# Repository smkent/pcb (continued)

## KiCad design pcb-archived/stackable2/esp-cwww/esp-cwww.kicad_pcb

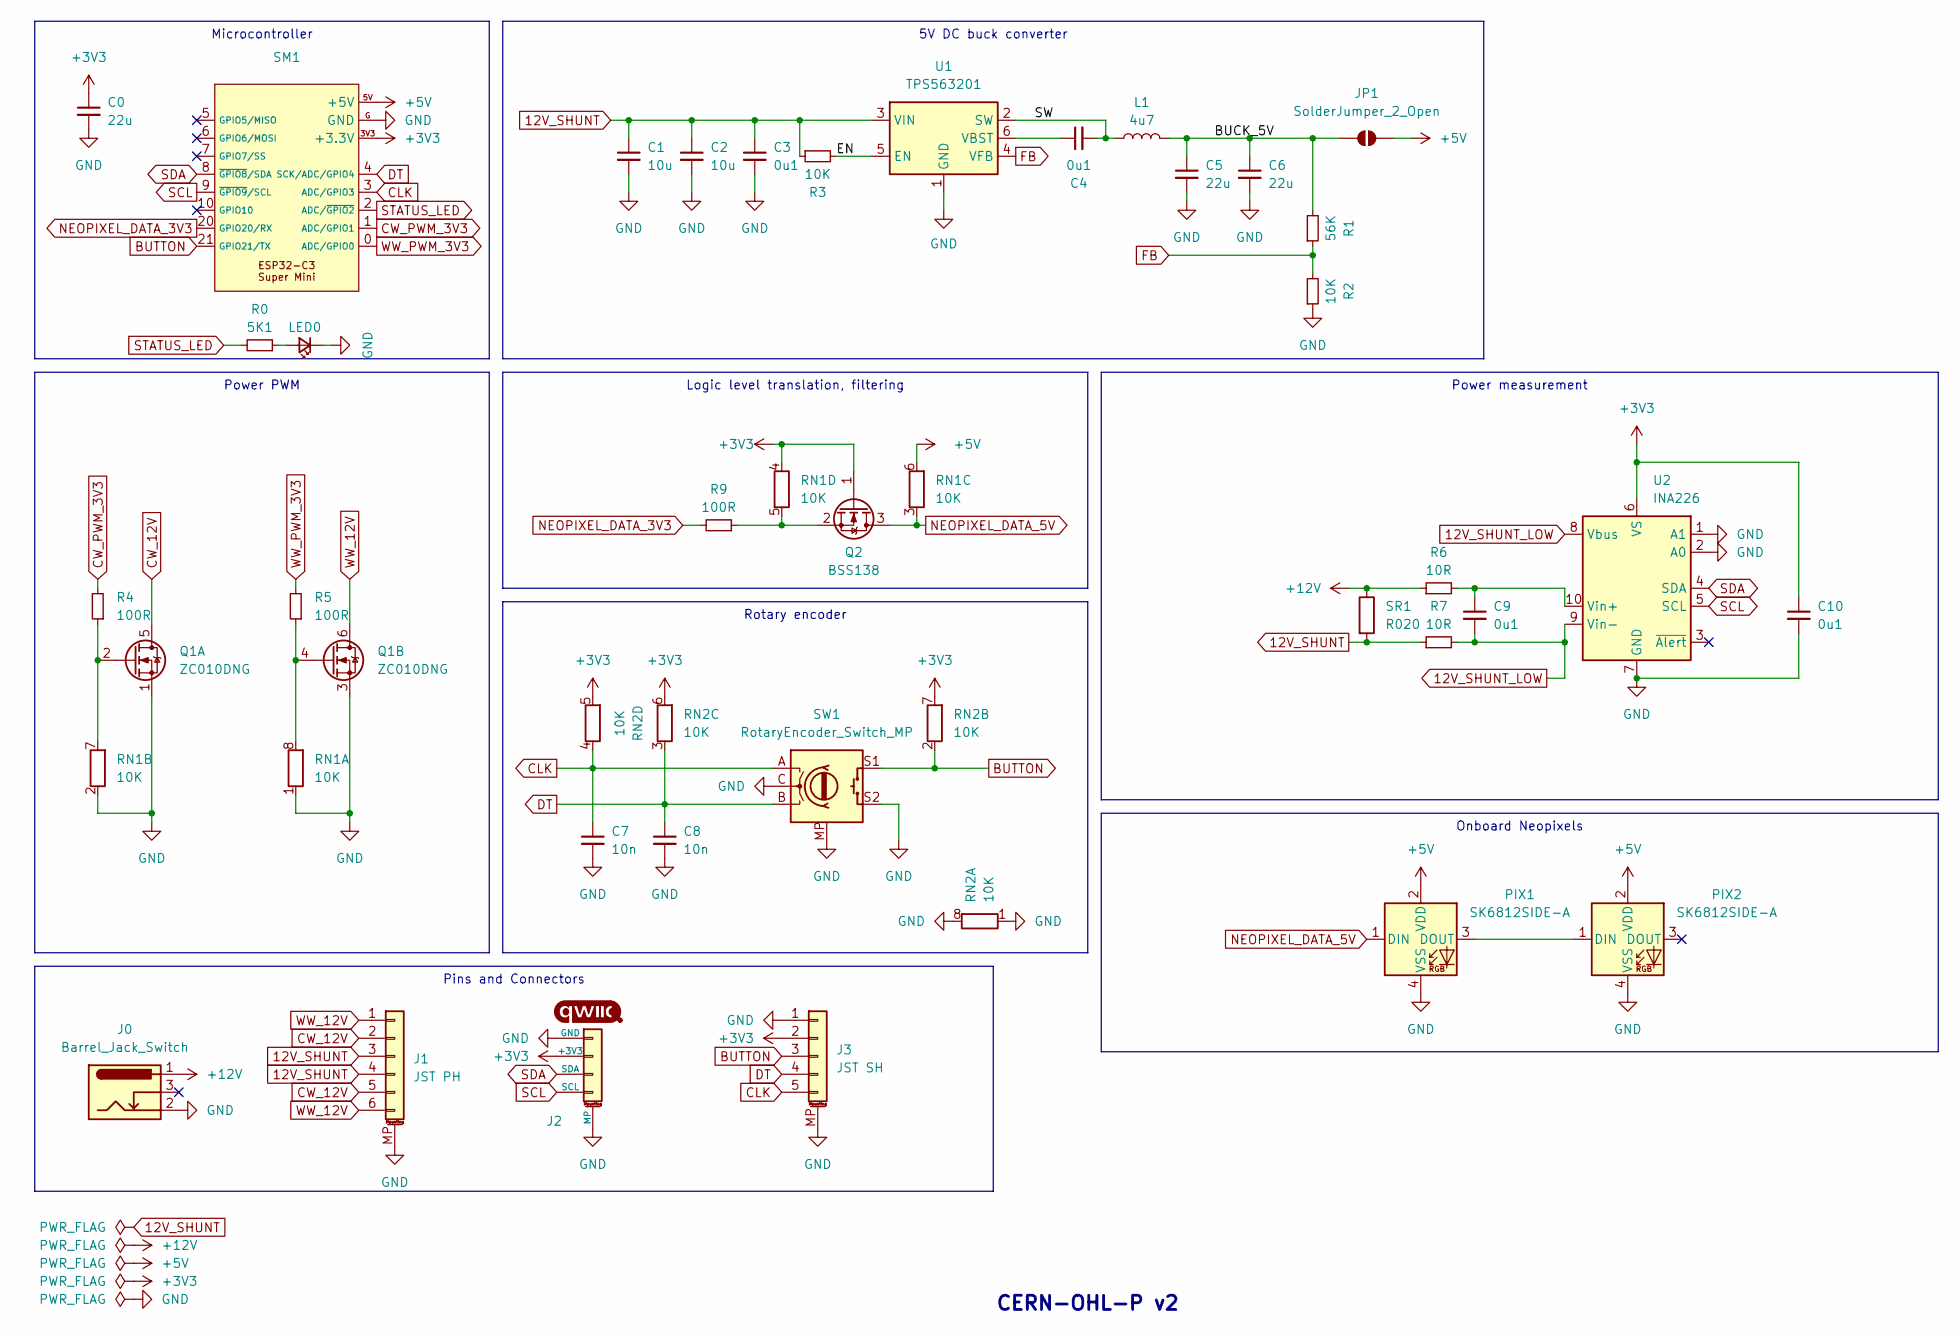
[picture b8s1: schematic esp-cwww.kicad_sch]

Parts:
C0, C5, C6: 22u; C_0603_1608Metric_Pad1.08x0.95mm_HandSolder
C1, C2: 10u; C_0603_1608Metric_Pad1.08x0.95mm_HandSolder
C3, C4: 0u1; C_0603_1608Metric_Pad1.08x0.95mm_HandSolder
C7, C8: 10n; C_0603_1608Metric_Pad1.08x0.95mm_HandSolder
C9, C10: 0u1; C_0402_1005Metric; LCSC Part C152814
J0: Barrel_Jack_Switch; BarrelJack_DC-050_SMT_Horizontal
J1: JST PH; JST_PH_S6B-PH-SM4-TB_1x06-1MP_P2.00mm_Horizontal
J2: Qwiic; Qwiic-SMD-horizontal-logo
J3: JST SH; JST_SH_SM05B-SRSS-TB_1x05-1MP_P1.00mm_Horizontal
JP1: SolderJumper_2_Open; SolderJumper-2_P1.3mm_Open_TrianglePad1.0x1.5mm
L1: 4u7; L_1008_2520Metric
LED0: LED_Small; LED_0603_1608Metric_Pad1.05x0.95mm_HandSolder_simple
PIX1, PIX2: SK6812SIDE-A; LED_SK6812SIDE-A_4.0x1.6mm; LCSC Part C2890037
Q1: ZC010DNG; PDFN-8_L3.2-W3.1-P0.65-LS3.4-BL-EP2; LCSC Part C36499170
Q2: BSS138; SOT-23
R0: 5K1; R_0402_1005Metric
R1: 56K; R_0603_1608Metric_Pad0.98x0.95mm_HandSolder
R2, R3: 10K; R_0603_1608Metric_Pad0.98x0.95mm_HandSolder
R4, R5, R9: 100R; R_0603_1608Metric_Pad0.98x0.95mm_HandSolder
R6, R7: 10R; R_0402_1005Metric; LCSC Part C25077
RN1, RN2: 10K; R_Array_Convex_4x0603
SM1: ESP32-C3-Super-Mini-Castellated-SMD-only
SR1: R020; R_2512_6332Metric_Pad1.40x3.35mm_HandSolder; LCSC Part C5375467
SW1: RotaryEncoder_Switch_MP; RotaryEncoder_Alps_EC11-Switch_Combo_H20mm
U1: TPS563201; SOT-23-6
U2: INA226; VSSOP-10_3x3mm_P0.5mm

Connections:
12V_SHUNT: C1.1, C2.1, C3.1, J1.3, J1.4, R3.1, R7.1, SR1.2, U1.3 (VIN)
12V_SHUNT_LOW: C9.2, R7.2, U2.8 (Vbus), U2.9 (Vin-)
+3V3: C0.1, C10.1, J2.2 (+3V3), J3.2, Q2.1 (G), RN1.4 (R4.1), RN2.5 (R4.2), RN2.6 (R3.2), RN2.7 (R2.2), SM1.3V3 (+3.3V), U2.6 (VS)
+5V: JP1.2 (B), PIX1.2 (VDD), PIX2.2 (VDD), RN1.6 (R3.2), SM1.5V (+5V)
+12V: J0.1, R6.1, SR1.1
/BUCK_5V: C5.1, C6.1, JP1.1 (A), L1.2, R1.2
/EN: R3.2, U1.5 (EN)
/SW: C4.2, L1.1, U1.2 (SW)
BUTTON: J3.3, RN2.2 (R2.1), SM1.21 (GPIO21/TX), SW1.S1
CLK: C7.1, J3.5, RN2.4 (R4.1), SM1.3 (ADC/GPIO3), SW1.A
CW_12V: J1.2, J1.5, Q1.5 (D)
CW_PWM_3V3: R4.2, SM1.1 (ADC/GPIO1)
DT: C8.1, J3.4, RN2.3 (R3.1), SM1.4 (SCK/ADC/GPIO4), SW1.B
FB: R1.1, R2.2, U1.4 (VFB)
GND: C0.2, C1.2, C2.2, C3.2, C5.2, C6.2, C7.2, C8.2, C10.2, J0.2, J1.MP (MountPin), J2.1 (GND), J2.MP, J3.1, J3.MP (MountPin), LED0.1 (K), PIX1.4 (VSS), PIX2.4 (VSS), Q1.1 (S), Q1.3 (S), R2.1, RN1.1 (R1.1), RN1.2 (R2.1), RN2.1 (R1.1), RN2.8 (R1.2), SM1.G (GND), SW1.C, SW1.MP, SW1.S2, U1.1 (GND), U2.1 (A1), U2.2 (A0), U2.7 (GND)
NEOPIXEL_DATA_3V3: R9.2, SM1.20 (GPIO20/RX)
NEOPIXEL_DATA_5V: PIX1.1 (DIN), Q2.3 (D), RN1.3 (R3.1)
unnamed: LED0.2 (A), R0.1
unnamed: PIX1.3 (DOUT), PIX2.1 (DIN)
unnamed: Q1.2 (G), R4.1, RN1.7 (R2.2)
unnamed: Q1.4 (G), R5.1, RN1.8 (R1.2)
unnamed: Q2.2 (S), R9.1, RN1.5 (R4.2)
unnamed: C4.1, U1.6 (VBST)
unnamed: C9.1, R6.2, U2.10 (Vin+)
SCL: J2.4 (SCL), SM1.9 (~GPIO9/SCL), U2.5 (SCL)
SDA: J2.3 (SDA), SM1.8 (~GPIO8/SDA), U2.4 (SDA)
STATUS_LED: R0.2, SM1.2 (ADC/~GPIO2)
WW_12V: J1.1, J1.6, Q1.6 (D)
WW_PWM_3V3: R5.2, SM1.0 (ADC/GPIO0)

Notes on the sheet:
Rotary encoder
5V DC buck converter
Onboard Neopixels
Logic level translation, filtering
Power PWM
Power measurement
Pins and Connectors
Microcontroller
CERN-OHL-P v2

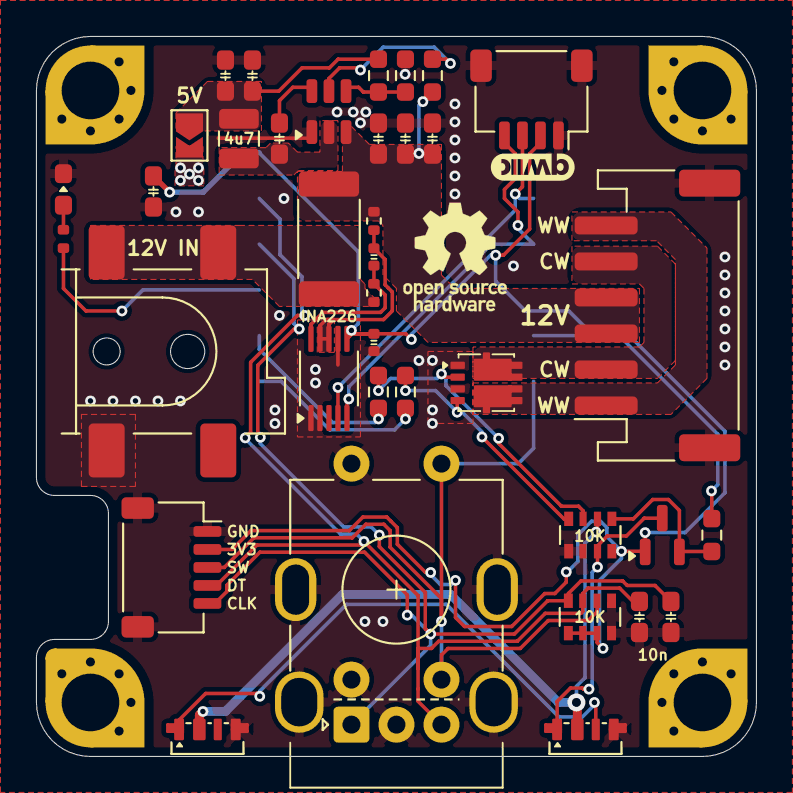
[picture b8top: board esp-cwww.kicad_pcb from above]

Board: 2 copper layers, 40.0 x 40.0 mm, 38 parts (1 on the bottom side), 29 nets.

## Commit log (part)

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2024-12-16 Migrate `ZC010DNG` symbol from `lcsc` to `discrete`
2024-12-16 Migrate `SDV301N3` symbol from `lcsc` to `discrete`
2024-12-16 Update `lcsc` RGB LED symbol values to match their names
2024-12-16 Migrate `XL-B1010RGBT-HF` symbol from `lcsc` to `discrete`
2024-12-16 Remove unused `P4-1204RGBWS2-1.5T-A` symbol, footprint, and model
2024-12-16 Add LCSC part number to `FM-3510RGBA-SG` symbol
2024-12-16 Remove no longer used `E6C0805RQBC2UDA` symbol, footprint, and model
2024-12-16 Migrate `VEML6030`, `VEML7700` symbols from `lcsc` to `discrete`
2024-12-16 Migrate `TEMT6000X01` symbol from `lcsc` to `discrete`
2024-12-16 Update silkscreen overlap DRC exclusion on esp-3dp
2024-12-16 Migrate `MAX17048` symbol from `lcsc` to `ic`
2024-12-16 Migrate `MT3608` symbol from `lcsc` to `ic`
2024-12-16 Migrate `ETA3485` symbol from `lcsc` to `ic`
2024-12-16 Migrate `ME6211C33U4` symbol from `lcsc` to `ic`
2024-12-16 Migrate `XTP2021-180AD1CT` symbol from `lcsc` to `ic`
2024-12-16 Migrate `ZD8028IB5TR` symbol from `lcsc` to `ic`
2024-12-16 Rework XB3306D symbol to match layout of KiCAD built-in BMS symbols
2024-12-16 Migrate `HUSB237-AA001-DN06R` symbol from `lcsc` to `ic`
2024-12-16 Restore correct XD3306D circuit in eta6003
2024-12-16 Rework `HLK-LD2410C` to match KiCAD symbol conventions
2024-12-16 Rework `AHT20+BMP280` symbol to match KiCAD symbol conventions
2024-12-16 Update `ESP32-C3-Super-Mini` symbol in garage-door-control schematic
2024-12-16 Recreate `74LVC2G00HD4-7` symbol as a single combined unit
2024-12-16 Add HT-3H4-B symbol
2024-12-16 Add AT3H7D symbol, footprint, and 3D model
2024-12-16 Add MB10F symbol, footprint, and 3D model
2024-12-16 Create symbol for `SN74LVC1T45Z6`
2024-12-16 Add `DY-IRMA381` derived symbol
2024-12-16 Create `Infrared-Receiver-Module` symbol in `interactive`
2024-12-16 Rework side-mount 1.7x1.1mm LED footprint as `LED_SideEmitter_1.7x1.1mm`
2024-12-16 Add 1206 LED, IR LED footprints and 3D models
2024-12-17 Update net names in garage-door-control for updated ESP32-C3 symbol
2024-12-17 Migrate `LED_0805_2012Metric` from `led` to `discrete`
2024-12-17 Migrate `LED_SK6812_PLCC4_5.0x5.0mm_P3.2mm` from `led` to `discrete`
2024-12-17 Migrate `LED_0603_1608Metric` from `led` to `discrete`
2024-12-17 Remove now-unused `led` footprint library
2024-12-17 Rename `SK6812SIDE-A` footprint, tweak silkscreen, add symbol part #
2024-12-17 Migrate XL-1615RGBC footprint to `discrete`
2024-12-17 Remove unused footprint `LED-SMD_L3.2-W2.8-TR` and models from `lcsc`
2024-12-17 Rework P4-1209RGBTCA1-0.9T-A footprint, migrate to `discrete`
2024-12-17 Replace 5730 LED footprint in `discrete` footprint library
2024-12-17 Recreate potentiometer footprint in `discrete` footprint library
2024-12-17 Migrate VEML6030, VEML7700 footprints from `lcsc` to `discrete`
2024-12-17 Create SMD and THT barrel jack footprints
2024-12-17 Migrate esp-rgb-driver to new DC-050 DC jack footprint
2024-12-17 Remove obsolete `DC-IN_DC-050-2.0-BB{,_rev2}` footprints
2024-12-17 Migrate Infrared Receiver Module (IRM) symbols to `discrete` library
2024-12-17 Create `electromechanical` footprint library
2024-12-17 Migrate buck-tps563201 to use `SW_SPDT_PCM12` footprint
2024-12-17 Add footprint filter to `SW_SPDT_MountingPin` symbol
2024-12-17 Migrate breadboard-power to use `SW_SPDT_PCM12` footprint
2024-12-17 Rework, migrate small SMD push button footprint to `electromechanical`
2024-12-17 Remove unused `Push-Button-SMD-4x4x1.5mm\*` footprints
2024-12-17 Migrate `SW_Push_DPDT_Toggle_7.0x7.0mm` to `electromechanical`
2024-12-17 Rework 18650 battery holder footprint, migrate to `connector`
2024-12-17 Migrate `SW_DIP_SPSTx04_Slide_P1.27mm` footprint to `electromechanical`
2024-12-17 Migrate ETA6003 custom QFN footprint to `package`
2024-12-17 Rework, migrate TEMT6000X01 footprint from `custom` to `discrete`
2024-12-17 Update courtyard overlap DRC exclusion in esp-cwww
2024-12-17 Rename custom USB-C 16P receptacle footprint to match source footprint
2024-12-17 Move `WDFN-10-1EP_3x3mm_P0.5mm_EP1.8x2.5mm_ThermalVias_half` to package
2024-12-17 Retire and remove `SOT-23-5_HandSoldering_simple` footprint
2024-12-17 Migrate `D_SOD-323_HandSoldering` footprint to `package`
2024-12-17 Migrate 0805 capacitor wide-center hand soldering footprint to `discrete`
2024-12-17 Migrate 0603 capacitor hand soldering footprint to `discrete`
2024-12-17 Remove `TerminalBlock_Phoenix_MKDS-1,5-3_1x03_P5.00mm_Horizontal_simple`
2024-12-17 Remove obsolete custom pad 3.5mm 1x02 terminal block footprint
2024-12-17 Remove obsolete `TerminalBlock_or_JST_2.54_1x02` footprint
2024-12-17 Remove `LED_WS2812B_PLCC4_5.0x5.0mm_P3.2mm_simple_small_courtyard`
2024-12-17 Update lcd-round to use KiCAD built-in discrete footprints
2024-12-17 Reduce custom footprint use on esp-doorbell-dev
2024-12-17 Reduce custom footprint use on 555-timer
2024-12-17 Remove unused and obsolete connector combo custom footprints
2024-12-17 Remove unused and obsolete custom JST XH connector footprints
2024-12-17 Retire and remove `Inductor_Multi_5.2x5.7_2x2.5` footprint
2024-12-17 Recreate JST XH 1x02 2AW connector footprint based on built-in footprint
2024-12-17 Add JST XH 1x04 2AW connector footprint
2024-12-17 Adjust JST XH 2AW 3D model scaling
2024-12-17 Add `SW_Slide-03_DPDT_9.1x3.5mm_P2.50mm_THT` footprint and model
2024-12-17 Add PJ-3062 symbol
2024-12-17 Correct 1.27mm pitch IRM footprint
2024-12-18 Update buck-tps563201 courtyard overlap DRC exclusions
2024-12-18 Migrate garage-door-control to use `BarrelJack_DC-050_SMT_Horizontal`
2024-12-18 Set mounting pin pad numbers to MP on mini tactile switch footprint
2024-12-18 Create symbol for SP4T slide switch, SS-14D01-G020
2024-12-18 Add BAT60B symbol
2024-12-18 Add exterior polarity indicator to SOD-123F footprint
2024-12-18 Recreate symbol for TEMT6000X01
2024-12-18 Add MM5Z10 Zener diode symbol
2024-12-18 Add USB-C 6P and 16P receptacle symbols
2024-12-18 Add TPS563201DDCR buck converter IC symbol
2024-12-19 Create IR LED symbols
2024-12-19 Reduce `SW_Slide_SP4T_MountingPin` symbol size
2025-01-09 Move OSHW logo in schematic templates to title box
2025-01-19 Update DRC exclusions in breadboard-power-microcontroller
2025-01-20 Update DRC exclusions in breadboard-power
2025-01-20 Update DRC exclusions in reflow jig
2025-01-20 Add customized symbol and footprint for `ESP32-C3-WROOM-02`
    1
2025-01-21 Add LCSC part number to `SN74LVC1G157DC` symbol
2025-01-21 Duplicate KiCAD SOT-523 footprint in `packages` with LCSC 3D model
2025-01-21 Reduce silkscreen outline on `Jack_3.5mm_PJ-327U-SMT_Horizontal`
2025-01-21 Update GND thermal relief connection angle to 45° in USB-C 16P footprint
2025-01-21 Add new N-channel MOSFET part symbols
2025-01-24 Add symbol, footprint, and models for `SN74HCS165BQBR`
2025-01-24 Add EP ground pin to `SN74HCS165BQBR` symbol
2025-01-24 Set USB-C connector footprint types to through-hole
2025-01-25 Reroute buck IC enable trace, tweak schematic placements for readability
2025-01-26 Change esp-av boot tactile button type
2025-01-29 Create more compact M3 mounting hole mechanical footprints
2025-01-30 Fix ESP32-{C,S}3 Super Mini THT/SMD combo footprint pads
2025-01-31 Adjust courtyard on `ESP32-C3-WROOM-02` footprint
2025-01-31 Create stackable3/esp-av
2025-01-31 Tweak stackable3/esp-av schematic box formatting
2025-02-01 In build, remove lib symlink target if it's an empty directory
2025-02-01 Add status / fuse LED icons to stackable3 3dp, cwww boards
2025-02-01 Use 2x0402 resistor array for I2C in stackable3/esp-neopixel-driver
2025-02-02 Add LEDs for unused GPIOs
2025-02-02 Update `XL-1606UWC` symbol description
2025-02-02 Adjust schematic positioning on stackable3/esp-3dp
2025-02-03 Update courtyard on `IRM_5.0x5.0mm_SIP-3_P1.27mm_THT` footprint
2025-02-03 Add more ground vias
2025-02-03 Tweak silkscreen on stackable3 boards
2025-02-03 Update buck converter labeling in stackable3 board schematics
2025-02-03 Change GPIO assignments on stackable3/esp-av
    This prevents the IR transmitter and shift register from boot and
    firmware update-related transient states
2025-02-03 Tweak traces
2025-02-04 Tweak power traces on stackable3/esp-av
2025-02-04 Change repeater enable silkscreen text
2025-02-04 Rearrange power capacitors
2025-02-04 Rearrange silkscreen title, logos
2025-02-05 Add LCSC Part number to `G2N7002X` symbol
2025-02-06 Create stackable3/shift-registers-74hc165
2025-02-06 Add month to silkscreen dates on stackable3 boards
2025-02-06 Create stackable3/ir-trx
2025-02-08 Use new JST SH rotary encoder connector symbol in rotary encoder module
2025-02-08 Use new JST SH rotary encoder connector symbol in stackable3/esp-cwww
2025-02-08 Use new JST SH rotary encoder connector symbol in stackable3/esp-av
2025-02-08 Use new JST SH rotary encoder symbol in stackable3/esp-rgb-driver
2025-02-08 Add 3 more neopixels to stackable3/esp-3dp, label as "RGB"
2025-02-08 Label neopixel channels as "RGB" on stackable3/esp-neopixel-driver
2025-02-08 Move jigs/esp-doorbell-button to pcb-archived
2025-02-08 Move power/buck-tps563201 to pcb-archived
2025-02-08 Update URL to pcb.smkent.net on remaining boards
2025-02-09 Update stackable3/esp-av IR repeater control circuit
    This replaces the N-channel repeater signal control MOSFET with a
    P-channel MOSFET (driven by an N-channel MOSFET at -5V)
2025-02-11 Rework misc/esp-doorbell-dev as stackable3/esp-doorbell-dev board
    This removes the previous fab outputs for misc/esp-doorbell-dev
2025-02-13 Create stackable3/power-selector-dev
2025-02-13 Create stackable3/esp-doorbell-dev fab outputs for new order
2025-02-13 Add LCSC Part number to stackable3/esp-cwww 1x04 JST PH connector
2025-02-13 Tweak stackable3/shift-registers-74hc595 schematic
2025-02-13 Fix net label direction, tweak schematic on stackable3/esp-av
2025-02-13 Fix rotary encoder net label directions on stackable3/esp-cwww
2025-02-13 Fix rotary encoder net label directions on stackable3/esp-3dp
2025-02-13 Rename rotary encoder nets on stackable3/esp-3dp
2025-02-13 Fix `IO0/SW/DATA` net label direction on stackable3/esp-neopixel-driver
2025-02-13 Add LCSC Part number to R8 on stackable3/esp-av
2025-02-13 Add LCSC part number to 1206 resistors on stackable3/ir-trx
2025-02-14 Create stackable3/esp-av fab outputs for new order
2025-02-14 Create stackable3/esp-3dp fab outputs for new order
2025-02-14 Create stackable3/esp-neopixel-driver fab outputs for new order
2025-02-14 Create stackable3/shift-registers-74hc595 fab outputs for new order
2025-02-14 Create stackable3/esp-cwww-5v
2025-02-20 Change C1 value to 1u
2025-03-08 Fix silkscreen GPIO labels on stackable3/esp-neopixel-driver
2025-03-15 Add `SP2006KT5` symbol to `discrete`
2025-03-15 Add `GT0104SC` datasheet, symbol, and footprint
2025-03-15 Rework stackable3/esp-rgb-driver as v3
    - Add pull-up resistors to inverter inputs
    - Add optional onboard 1x1 RGB LEDs for each output channel
2025-03-15 Create stackable3/quad-level-shifter-gt0104sc
2025-03-15 Remove redundant power traces from quad-level-shifter-gt0104sc
2025-03-18 Create stackable3/flexypin-esp32c3-wroom-jig
2025-03-19 Support overriding `generate_interactive_bom` path via `IBOM` env var
2025-03-19 Adjust OSHW logo position in schematic templates
2025-03-19 Add project info to stackable3/quad-level-shifter-gt0104sc
2025-03-19 Organize stackable3/esp-cwww-5v schematic
2025-03-19 Add project info to stackable3/esp-rgb-driver
2025-03-19 Add LCSC part numbers to stackable3/flexypin-esp32c3-wroom-jig
2025-03-19 Generate fab outputs for misc/rotary-encoder-module
2025-03-19 Generate fab outputs for stackable3/flexypin-esp32c3-wroom-jig
2025-04-05 Add symbols for new MOSFET parts
2025-04-16 Add, update DS8242 symbols in library
2025-04-16 Update stackable3/esp-av to v2
    Feature changes:
    - Add 38kHz RX signal modulation
    - Add onboard infrared receiver module (IRM)
    - Add JST SH connector for 595 daisy chain outputs
    - Add transmit pin socket connector tied to TX1
    - Remove neopixel daisy-chain output connectors
2025-04-17 Update stackable3/flexypin-esp32c3-wroom-jig to KiCAD 9 format
2025-04-17 Remove silkscreen rectangle from `BatteryHolder_1x18650_THT` footprint
2025-04-17 Increase rear silkscreen info font size on stackable3/esp-av
2025-04-17 Tweak MAX809, RN10, SW2 positions on stackable3/esp-av
